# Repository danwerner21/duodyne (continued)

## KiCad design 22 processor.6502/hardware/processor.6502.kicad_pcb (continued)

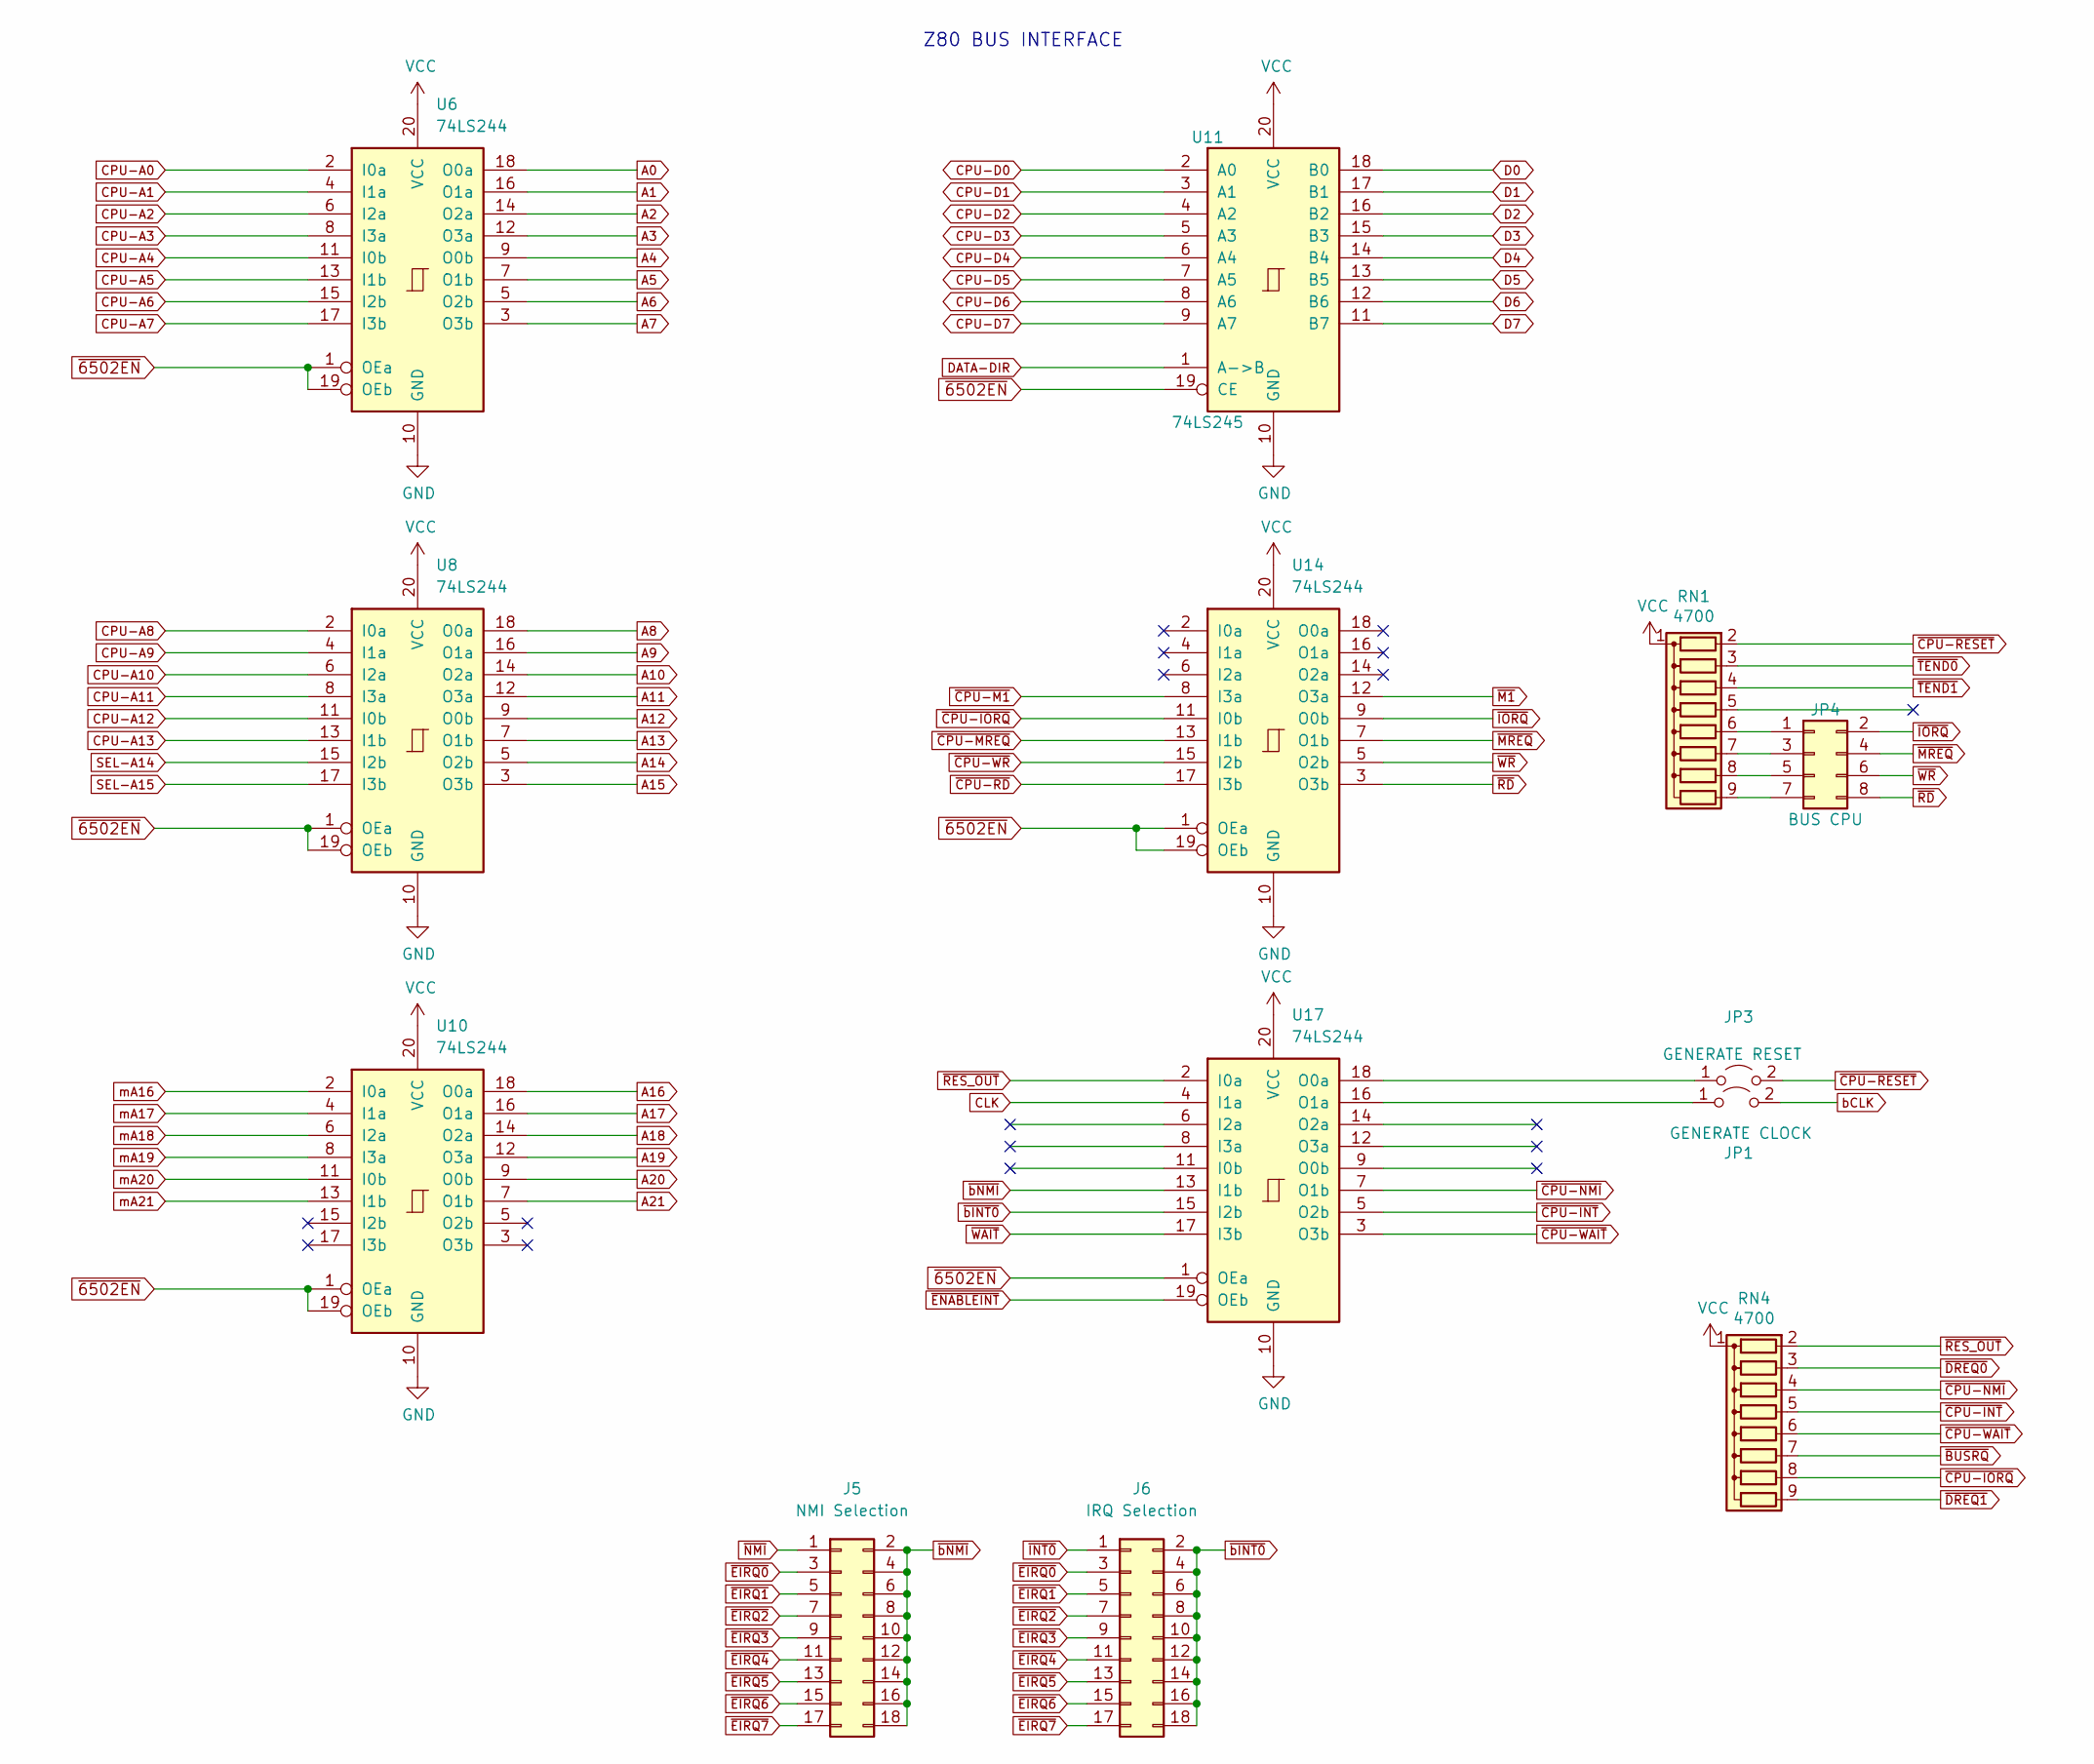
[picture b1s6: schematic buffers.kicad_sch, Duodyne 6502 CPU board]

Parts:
J5: NMI Selection; PinHeader_2x09_P2.54mm_Vertical
J6: IRQ Selection; PinHeader_2x09_P2.54mm_Vertical
JP1: GENERATE CLOCK; PinHeader_1x02_P2.54mm_Vertical
JP3: GENERATE RESET; PinHeader_1x02_P2.54mm_Horizontal
JP4: BUS CPU; PinHeader_2x04_P2.54mm_Vertical
RN1, RN4: 4700; R_Array_SIP9
U6, U8, U10, U14, U17: 74LS244; DIP-20_W7.62mm_Socket_LongPads
U11: 74LS245; DIP-20_W7.62mm_Socket_LongPads

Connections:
A0: U6.18 (O0a); also elsewhere on the board
A1: U6.16 (O1a); also elsewhere on the board
A2: U6.14 (O2a); also elsewhere on the board
A3: U6.12 (O3a); also elsewhere on the board
A4: U6.9 (O0b); also elsewhere on the board
A5: U6.7 (O1b); also elsewhere on the board
A6: U6.5 (O2b); also elsewhere on the board
A7: U6.3 (O3b); also elsewhere on the board
A8: U8.18 (O0a); also elsewhere on the board
A9: U8.16 (O1a); also elsewhere on the board
A10: U8.14 (O2a); also elsewhere on the board
A11: U8.12 (O3a); also elsewhere on the board
A12: U8.9 (O0b); also elsewhere on the board
A13: U8.7 (O1b); also elsewhere on the board
A14: U8.5 (O2b); also elsewhere on the board
A15: U8.3 (O3b); also elsewhere on the board
A16: U10.18 (O0a); also elsewhere on the board
A17: U10.16 (O1a); also elsewhere on the board
A18: U10.14 (O2a); also elsewhere on the board
A19: U10.12 (O3a); also elsewhere on the board
A20: U10.9 (O0b); also elsewhere on the board
A21: U10.7 (O1b); also elsewhere on the board
CLK: U17.4 (I1a); also elsewhere on the board
CPU-A0: U6.2 (I0a); also elsewhere on the board
CPU-A1: U6.4 (I1a); also elsewhere on the board
CPU-A2: U6.6 (I2a); also elsewhere on the board
CPU-A3: U6.8 (I3a); also elsewhere on the board
CPU-A4: U6.11 (I0b); also elsewhere on the board
CPU-A5: U6.13 (I1b); also elsewhere on the board
CPU-A6: U6.15 (I2b); also elsewhere on the board
CPU-A7: U6.17 (I3b); also elsewhere on the board
CPU-A8: U8.2 (I0a); also elsewhere on the board
CPU-A9: U8.4 (I1a); also elsewhere on the board
CPU-A10: U8.6 (I2a); also elsewhere on the board
CPU-A11: U8.8 (I3a); also elsewhere on the board
CPU-A12: U8.11 (I0b); also elsewhere on the board
CPU-A13: U8.13 (I1b); also elsewhere on the board
CPU-D0: U11.2 (A0); also elsewhere on the board
CPU-D1: U11.3 (A1); also elsewhere on the board
CPU-D2: U11.4 (A2); also elsewhere on the board
CPU-D3: U11.5 (A3); also elsewhere on the board
CPU-D4: U11.6 (A4); also elsewhere on the board
CPU-D5: U11.7 (A5); also elsewhere on the board
CPU-D6: U11.8 (A6); also elsewhere on the board
CPU-D7: U11.9 (A7); also elsewhere on the board
D0: U11.18 (B0); also elsewhere on the board
D1: U11.17 (B1); also elsewhere on the board
D2: U11.16 (B2); also elsewhere on the board
D3: U11.15 (B3); also elsewhere on the board
D4: U11.14 (B4); also elsewhere on the board
D5: U11.13 (B5); also elsewhere on the board
D6: U11.12 (B6); also elsewhere on the board
D7: U11.11 (B7); also elsewhere on the board
DATA-DIR: U11.1 (A->B); also elsewhere on the board
GND: U6.10 (GND), U8.10 (GND), U10.10 (GND), U11.10 (GND), U14.10 (GND), U17.10 (GND); also elsewhere on the board
unnamed: JP1.1 (A), U17.16 (O1a)
unnamed: JP3.1 (A), U17.18 (O0a)
unnamed: JP4.1, RN1.6 (R5)
unnamed: JP4.3, RN1.7 (R6)
unnamed: JP4.5, RN1.8 (R7)
unnamed: JP4.7, RN1.9 (R8)
SEL-A14: U8.15 (I2b); also elsewhere on the board
SEL-A15: U8.17 (I3b); also elsewhere on the board
VCC: RN1.1 (common), RN4.1 (common), U6.20 (VCC), U8.20 (VCC), U10.20 (VCC), U11.20 (VCC), U14.20 (VCC), U17.20 (VCC); also elsewhere on the board
bCLK: JP1.2 (B); also elsewhere on the board
mA16: U10.2 (I0a); also elsewhere on the board
mA17: U10.4 (I1a); also elsewhere on the board
mA18: U10.6 (I2a); also elsewhere on the board
mA19: U10.8 (I3a); also elsewhere on the board
mA20: U10.11 (I0b); also elsewhere on the board
mA21: U10.13 (I1b); also elsewhere on the board
~6502EN: U6.1 (OEa), U6.19 (OEb), U8.1 (OEa), U8.19 (OEb), U10.1 (OEa), U10.19 (OEb), U11.19 (CE), U14.1 (OEa), U14.19 (OEb), U17.1 (OEa); also elsewhere on the board
~BUSRQ: RN4.7 (R6); also elsewhere on the board
~CPU-INT: RN4.5 (R4), U17.5 (O2b); also elsewhere on the board
~CPU-IORQ: RN4.8 (R7), U14.11 (I0b); also elsewhere on the board
~CPU-M1: U14.8 (I3a); also elsewhere on the board
~CPU-MREQ: U14.13 (I1b); also elsewhere on the board
~CPU-NMI: RN4.4 (R3), U17.7 (O1b); also elsewhere on the board
~CPU-RD: U14.17 (I3b); also elsewhere on the board
~CPU-RESET: JP3.2 (B), RN1.2 (R1)
~CPU-WAIT: RN4.6 (R5), U17.3 (O3b); also elsewhere on the board
~CPU-WR: U14.15 (I2b); also elsewhere on the board
~DREQ0: RN4.3 (R2); also elsewhere on the board
~DREQ1: RN4.9 (R8); also elsewhere on the board
~EIRQ0: J5.3, J6.3; also elsewhere on the board
~EIRQ1: J5.5, J6.5; also elsewhere on the board
~EIRQ2: J5.7, J6.7; also elsewhere on the board
~EIRQ3: J5.9, J6.9; also elsewhere on the board
~EIRQ4: J5.11, J6.11; also elsewhere on the board
~EIRQ5: J5.13, J6.13; also elsewhere on the board
~EIRQ6: J5.15, J6.15; also elsewhere on the board
~EIRQ7: J5.17, J6.17; also elsewhere on the board
~ENABLEINT: U17.19 (OEb); also elsewhere on the board
~INT0: J6.1; also elsewhere on the board
~IORQ: JP4.2, U14.9 (O0b); also elsewhere on the board
~M1: U14.12 (O3a); also elsewhere on the board
~MREQ: JP4.4, U14.7 (O1b); also elsewhere on the board
~NMI: J5.1; also elsewhere on the board
~RD: JP4.8, U14.3 (O3b); also elsewhere on the board
~RES_OUT: RN4.2 (R1), U17.2 (I0a); also elsewhere on the board
~TEND0: RN1.3 (R2); also elsewhere on the board
~TEND1: RN1.4 (R3); also elsewhere on the board
~WAIT: U17.17 (I3b); also elsewhere on the board
~WR: JP4.6, U14.5 (O2b); also elsewhere on the board
~bINT0: J6.2, J6.4, J6.6, J6.8, J6.10, J6.12, J6.14, J6.16, J6.18, U17.15 (I2b)
~bNMI: J5.2, J5.4, J5.6, J5.8, J5.10, J5.12, J5.14, J5.16, J5.18, U17.13 (I1b)

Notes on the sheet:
Z80 BUS INTERFACE

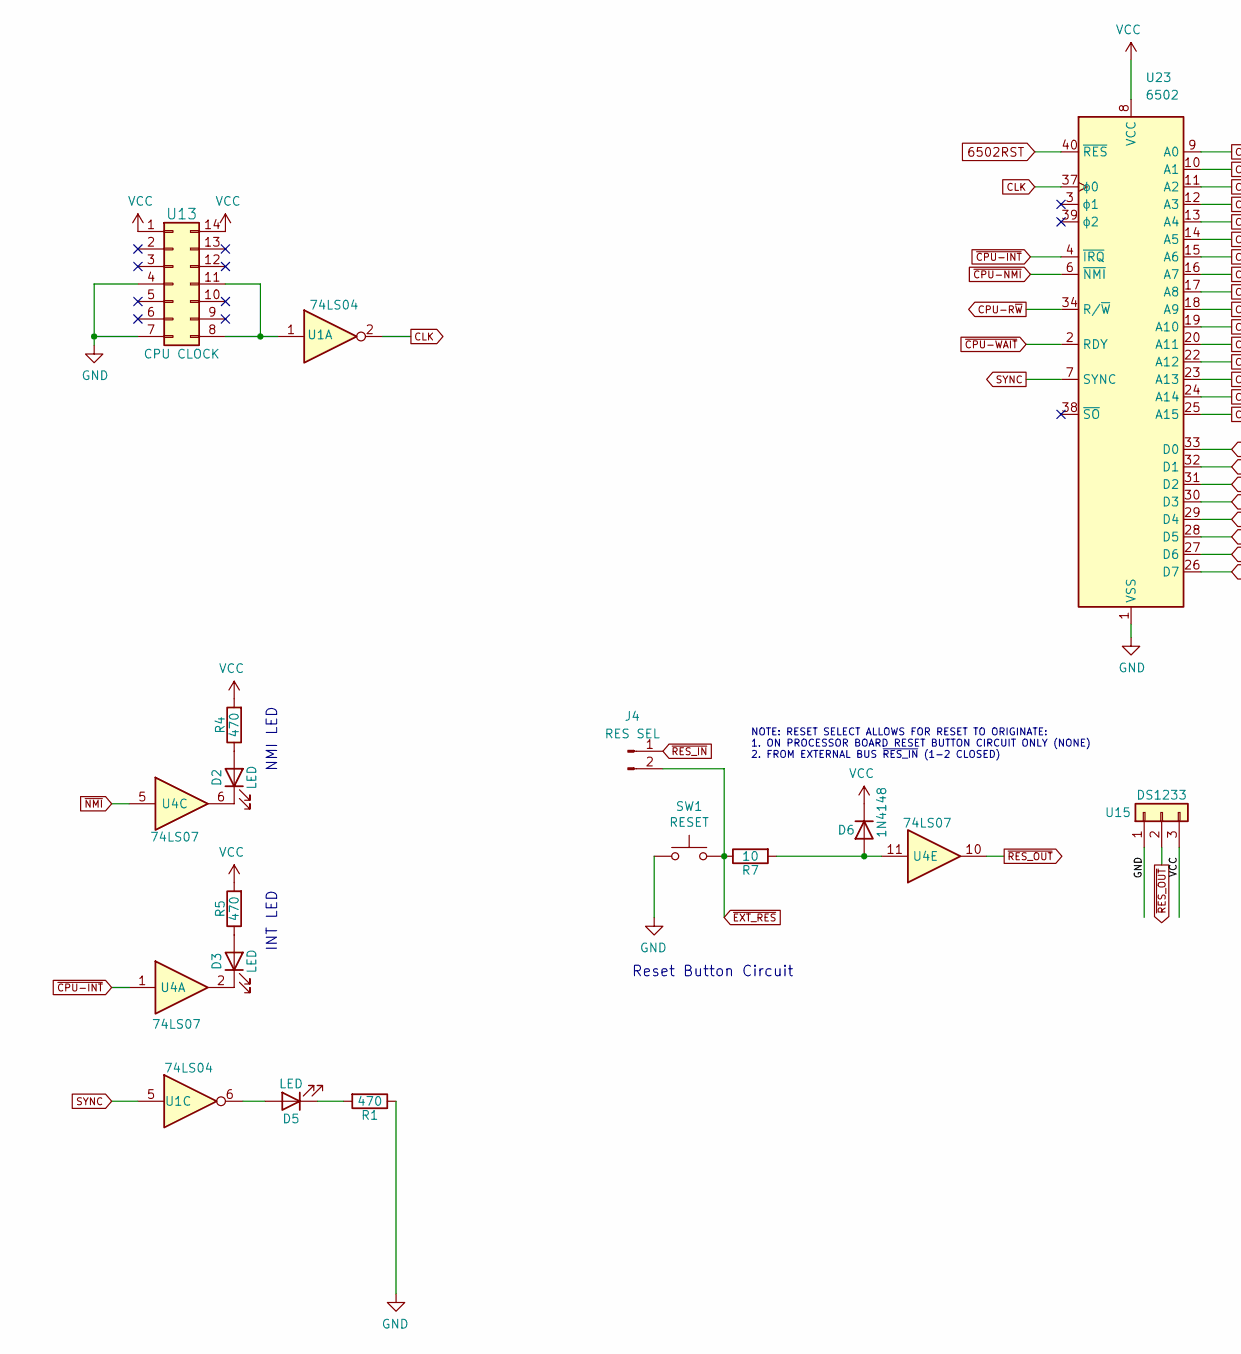
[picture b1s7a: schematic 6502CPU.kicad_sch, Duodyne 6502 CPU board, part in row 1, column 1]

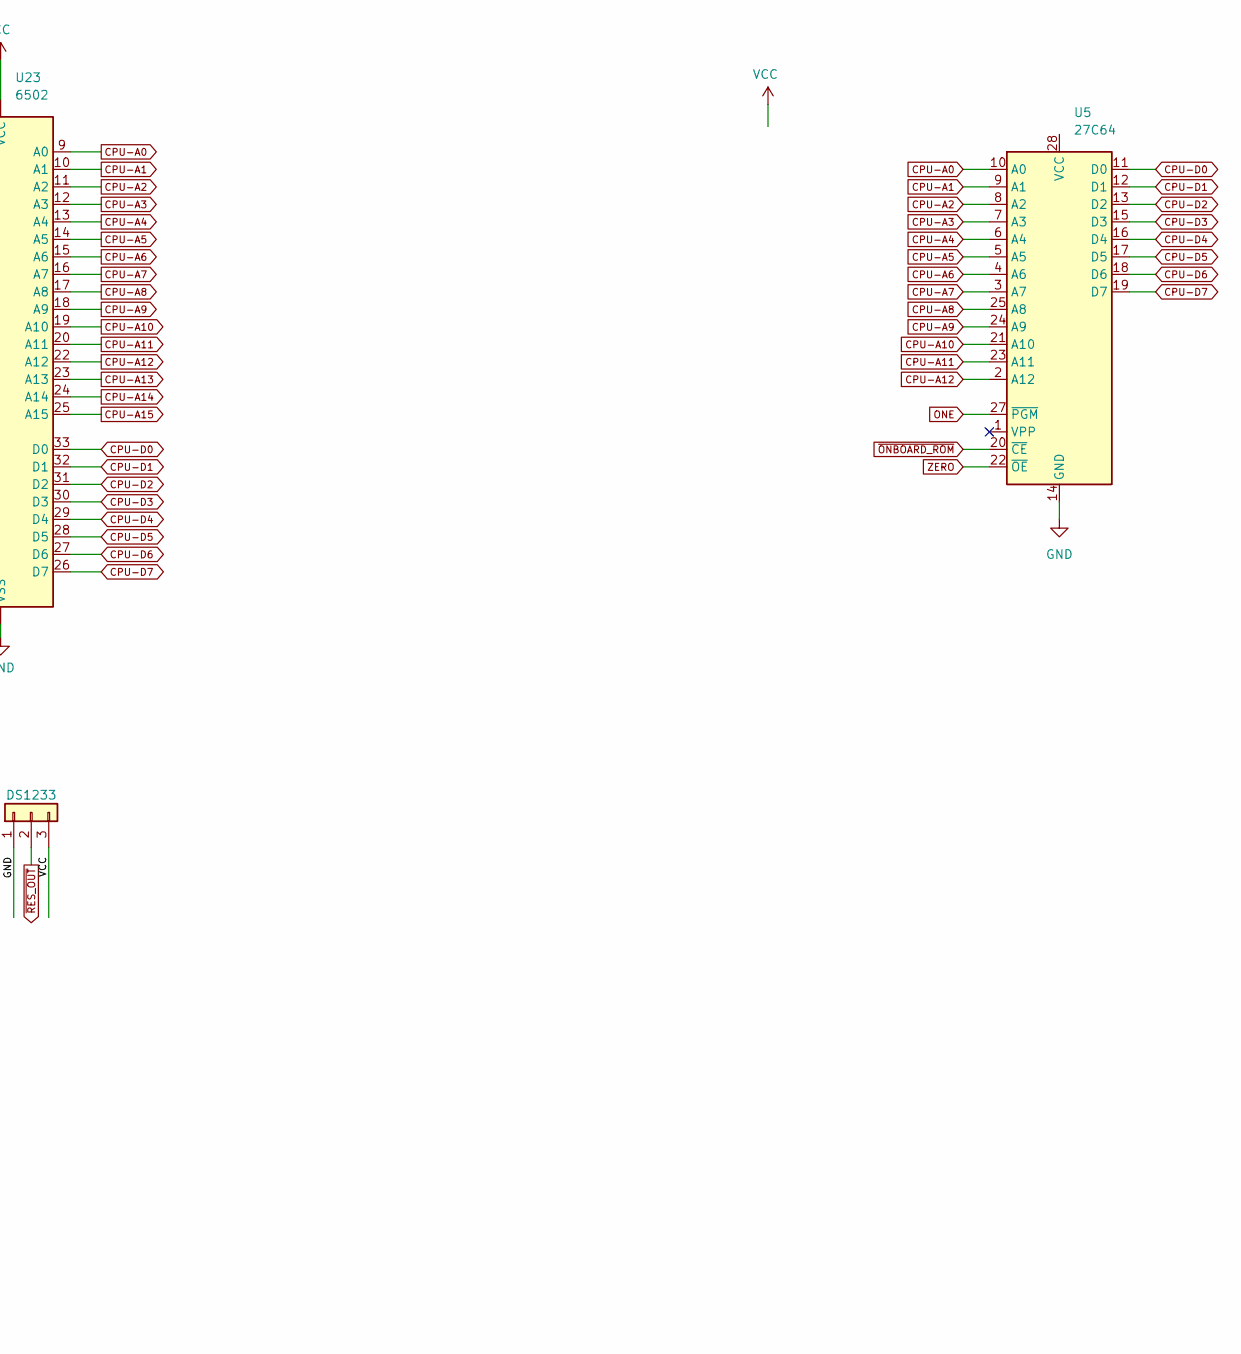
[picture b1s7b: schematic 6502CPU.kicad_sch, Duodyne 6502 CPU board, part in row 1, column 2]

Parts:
D2, D3, D5: LED; LED_D3.0mm_Horizontal_O3.81mm_Z2.0mm
D6: 1N4148; D_DO-35_SOD27_P7.62mm_Horizontal
J4: RES SEL; PinHeader_1x02_P2.54mm_Vertical
R1, R4, R5: 470; R_Axial_DIN0207_L6.3mm_D2.5mm_P7.62mm_Horizontal
R7: 10; R_Axial_DIN0207_L6.3mm_D2.5mm_P7.62mm_Horizontal
SW1: RESET; SW_Tactile_SPST_Angled_PTS645Vx58-2LFS
U1: 74LS04; DIP-14_W7.62mm_Socket_LongPads
U4: 74LS07; DIP-14_W7.62mm_Socket_LongPads
U5: 27C64; DIP-28_W15.24mm
U13: CPU CLOCK; DIP-14_W7.62mm_Socket_LongPads
U15: DS1233; TO-92L_HandSolder
U23: 6502; DIP-40_W15.24mm_Socket_LongPads

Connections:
6502RST: U23.40 (~RES); also elsewhere on the board
CLK: U1.2, U23.37 (ϕ0); also elsewhere on the board
CPU-A0: U5.10 (A0), U23.9 (A0); also elsewhere on the board
CPU-A1: U5.9 (A1), U23.10 (A1); also elsewhere on the board
CPU-A2: U5.8 (A2), U23.11 (A2); also elsewhere on the board
CPU-A3: U5.7 (A3), U23.12 (A3); also elsewhere on the board
CPU-A4: U5.6 (A4), U23.13 (A4); also elsewhere on the board
CPU-A5: U5.5 (A5), U23.14 (A5); also elsewhere on the board
CPU-A6: U5.4 (A6), U23.15 (A6); also elsewhere on the board
CPU-A7: U5.3 (A7), U23.16 (A7); also elsewhere on the board
CPU-A8: U5.25 (A8), U23.17 (A8); also elsewhere on the board
CPU-A9: U5.24 (A9), U23.18 (A9); also elsewhere on the board
CPU-A10: U5.21 (A10), U23.19 (A10); also elsewhere on the board
CPU-A11: U5.23 (A11), U23.20 (A11); also elsewhere on the board
CPU-A12: U5.2 (A12), U23.22 (A12); also elsewhere on the board
CPU-A13: U23.23 (A13); also elsewhere on the board
CPU-A14: U23.24 (A14); also elsewhere on the board
CPU-A15: U23.25 (A15); also elsewhere on the board
CPU-D0: U5.11 (D0), U23.33 (D0); also elsewhere on the board
CPU-D1: U5.12 (D1), U23.32 (D1); also elsewhere on the board
CPU-D2: U5.13 (D2), U23.31 (D2); also elsewhere on the board
CPU-D3: U5.15 (D3), U23.30 (D3); also elsewhere on the board
CPU-D4: U5.16 (D4), U23.29 (D4); also elsewhere on the board
CPU-D5: U5.17 (D5), U23.28 (D5); also elsewhere on the board
CPU-D6: U5.18 (D6), U23.27 (D6); also elsewhere on the board
CPU-D7: U5.19 (D7), U23.26 (D7); also elsewhere on the board
CPU-R~W: U23.34 (R/~W); also elsewhere on the board
GND: R1.1, SW1.2, U5.14 (GND), U13.4, U13.7, U15.1, U23.1 (VSS), U23.21 (VSS); also elsewhere on the board
unnamed: D2.1 (K), U4.6
unnamed: D2.2 (A), R4.1
unnamed: D3.1 (K), U4.2
unnamed: D3.2 (A), R5.1
unnamed: D5.1 (K), R1.2
unnamed: D5.2 (A), U1.6
unnamed: D6.2 (A), R7.2, U4.11
unnamed: U1.1, U13.8, U13.11
ONE: U5.27 (~PGM); also elsewhere on the board
SYNC: U1.5, U23.7 (SYNC)
VCC: D6.1 (K), R4.2, R5.2, U13.1, U13.14, U15.3, U23.8 (VCC); also elsewhere on the board
ZERO: U5.22 (~OE); also elsewhere on the board
~CPU-INT: U4.1, U23.4 (~IRQ); also elsewhere on the board
~CPU-NMI: U23.6 (~NMI); also elsewhere on the board
~CPU-WAIT: U23.2 (RDY); also elsewhere on the board
~EXT_RES: J4.2, R7.1, SW1.1; also elsewhere on the board
~NMI: U4.5; also elsewhere on the board
~ONBOARD_ROM: U5.20 (~CE); also elsewhere on the board
~RES_IN: J4.1; also elsewhere on the board
~RES_OUT: U4.10, U15.2; also elsewhere on the board

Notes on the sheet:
Reset Button Circuit
NMI LED
INT LED
NOTE: RESET SELECT ALLOWS FOR RESET TO ORIGINATE: 1. ON PROCESSOR BOARD RESET BUTTON CIRCUIT ONLY (NONE) 2. FROM EXTERNAL BUS ~{RES_IN} (1-2 CLOSED)

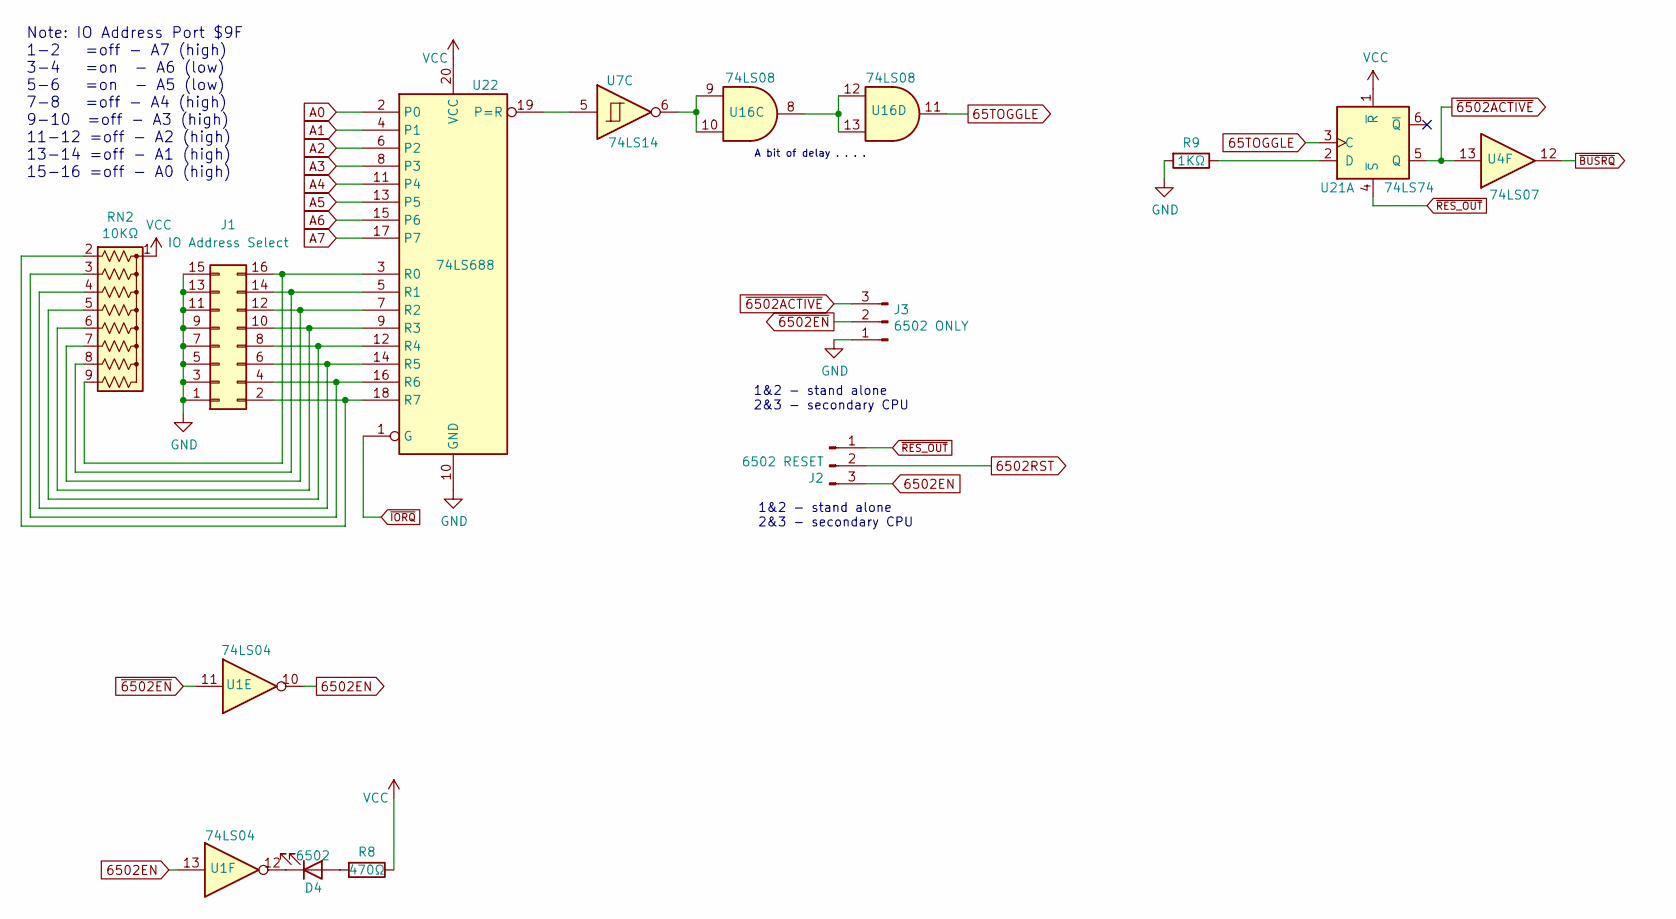
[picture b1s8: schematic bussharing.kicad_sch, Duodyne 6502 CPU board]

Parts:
D4: 6502; LED_D3.0mm_Horizontal_O3.81mm_Z2.0mm
J1: IO Address Select; PinHeader_2x08_P2.54mm_Vertical
J2: 6502 RESET; PinHeader_1x03_P2.54mm_Horizontal
J3: 6502 ONLY; PinHeader_1x03_P2.54mm_Horizontal
R8: 470Ω; R_Axial_DIN0207_L6.3mm_D2.5mm_P7.62mm_Horizontal
R9: 1KΩ; R_Axial_DIN0207_L6.3mm_D2.5mm_P7.62mm_Horizontal
RN2: 10KΩ; R_Array_SIP9
U1: 74LS04; DIP-14_W7.62mm_Socket_LongPads
U4: 74LS07; DIP-14_W7.62mm_Socket_LongPads
U7: 74LS14; DIP-14_W7.62mm_Socket_LongPads
U16: 74LS08; DIP-14_W7.62mm_Socket_LongPads
U21: 74LS74; DIP-14_W7.62mm_Socket_LongPads
U22: 74LS688; DIP-20_W7.62mm_Socket_LongPads

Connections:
65TOGGLE: U16.11, U21.3 (C)
6502EN: J2.3, U1.10, U1.13
6502RST: J2.2; also elsewhere on the board
A0: U22.2 (P0); also elsewhere on the board
A1: U22.4 (P1); also elsewhere on the board
A2: U22.6 (P2); also elsewhere on the board
A3: U22.8 (P3); also elsewhere on the board
A4: U22.11 (P4); also elsewhere on the board
A5: U22.13 (P5); also elsewhere on the board
A6: U22.15 (P6); also elsewhere on the board
A7: U22.17 (P7); also elsewhere on the board
GND: J1.1, J1.3, J1.5, J1.7, J1.9, J1.11, J1.13, J1.15, J3.1, R9.2, U22.10 (GND); also elsewhere on the board
unnamed: D4.1 (K), U1.12
unnamed: D4.2 (A), R8.2
unnamed: J1.2, RN2.2 (R1), U22.18 (R7)
unnamed: J1.4, RN2.3 (R2), U22.16 (R6)
unnamed: J1.6, RN2.4 (R3), U22.14 (R5)
unnamed: J1.8, RN2.5 (R4), U22.12 (R4)
unnamed: J1.10, RN2.6 (R5), U22.9 (R3)
unnamed: J1.12, RN2.7 (R6), U22.7 (R2)
unnamed: J1.14, RN2.8 (R7), U22.5 (R1)
unnamed: J1.16, RN2.9 (R8), U22.3 (R0)
unnamed: R9.1, U21.2 (D)
unnamed: U7.6, U16.9, U16.10
unnamed: U16.8, U16.12, U16.13
unnamed: U7.5, U22.19 (P=R)
VCC: R8.1, RN2.1 (common), U21.1 (~R), U22.20 (VCC); also elsewhere on the board
~6502ACTIVE: J3.3, U4.13, U21.5 (Q)
~6502EN: J3.2, U1.11; also elsewhere on the board
~BUSRQ: U4.12; also elsewhere on the board
~IORQ: U22.1 (G); also elsewhere on the board
~RES_OUT: J2.1, U21.4 (~S); also elsewhere on the board

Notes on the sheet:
1&2 - stand alone 2&3 - secondary CPU
A bit of delay . . . .
Note: IO Address Port $9F 1-2 =off - A7 (high) 3-4 =on - A6 (low) 5-6 =on - A5 (low) 7-8 =off - A4 (high) 9-10 =off - A3 (high) 11-12 =off - A2 (high) 13-14 =off - A1 (high) 15-16 =off - A0 (high)

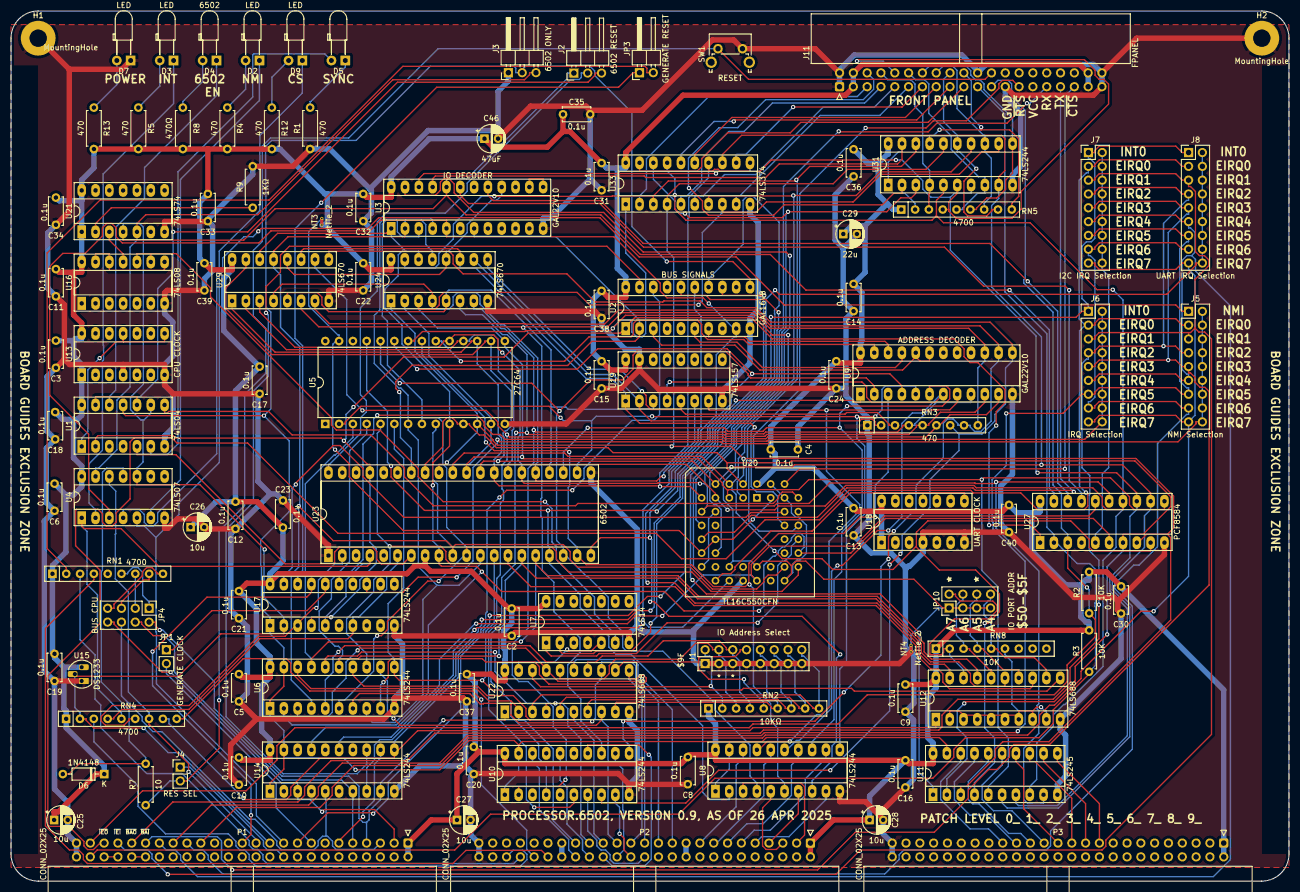
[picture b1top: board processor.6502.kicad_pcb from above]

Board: 2 copper layers, 235.0 x 160.0 mm, 111 parts (0 on the bottom side), 195 nets.

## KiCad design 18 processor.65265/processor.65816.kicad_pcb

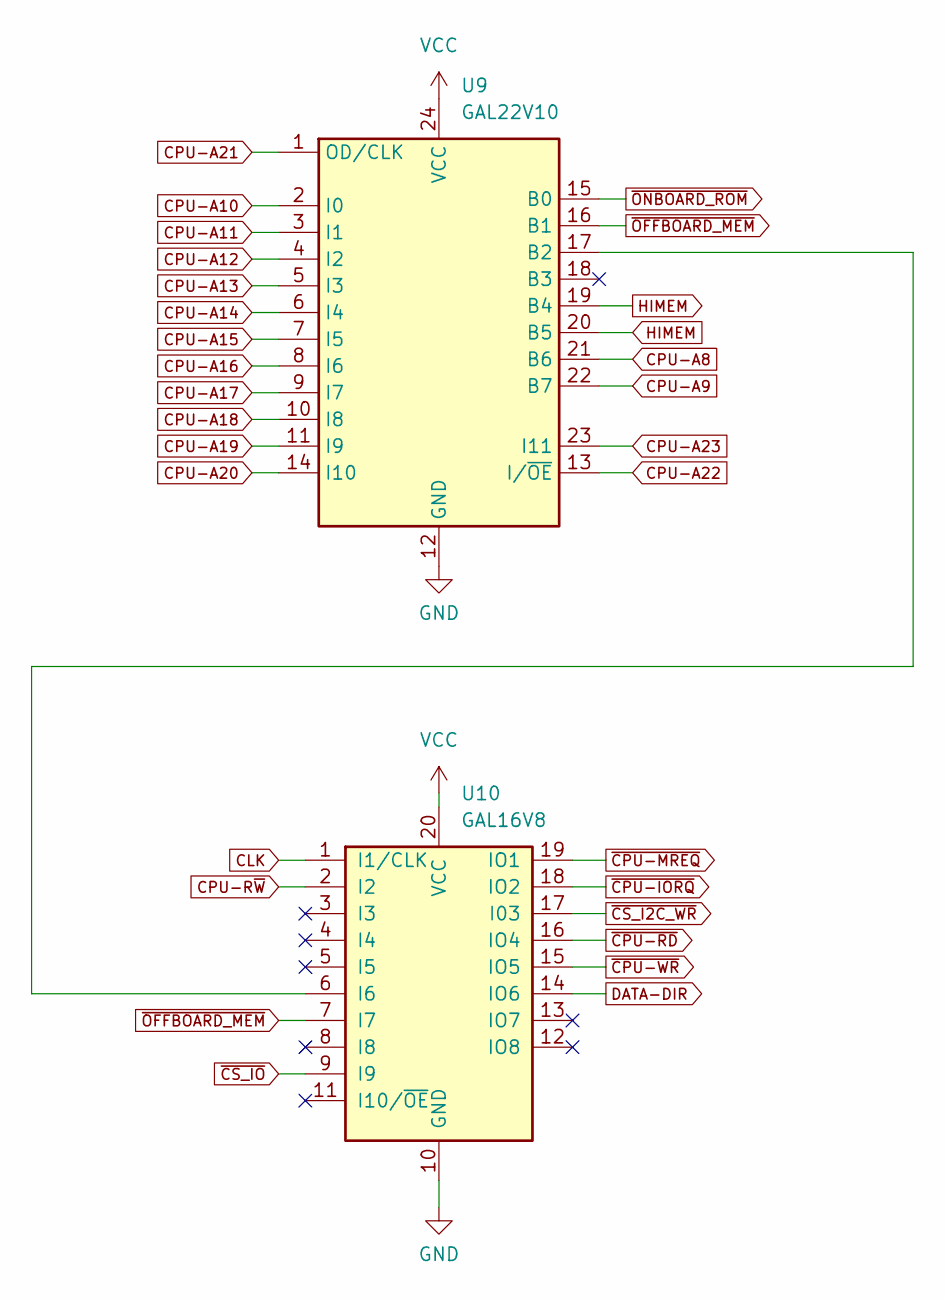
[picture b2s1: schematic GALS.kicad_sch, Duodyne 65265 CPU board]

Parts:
U9: GAL22V10; DIP-24_W7.62mm_Socket_LongPads
U10: GAL16V8; DIP-20_W7.62mm_Socket_LongPads

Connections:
CLK: U10.1 (I1/CLK); also elsewhere on the board
CPU-A8: U9.21 (B6); also elsewhere on the board
CPU-A9: U9.22 (B7); also elsewhere on the board
CPU-A10: U9.2 (I0); also elsewhere on the board
CPU-A11: U9.3 (I1); also elsewhere on the board
CPU-A12: U9.4 (I2); also elsewhere on the board
CPU-A13: U9.5 (I3); also elsewhere on the board
CPU-A14: U9.6 (I4); also elsewhere on the board
CPU-A15: U9.7 (I5); also elsewhere on the board
CPU-A16: U9.8 (I6); also elsewhere on the board
CPU-A17: U9.9 (I7); also elsewhere on the board
CPU-A18: U9.10 (I8); also elsewhere on the board
CPU-A19: U9.11 (I9); also elsewhere on the board
CPU-A20: U9.14 (I10); also elsewhere on the board
CPU-A21: U9.1 (OD/CLK); also elsewhere on the board
CPU-A22: U9.13 (I/~OE); also elsewhere on the board
CPU-A23: U9.23 (I11); also elsewhere on the board
CPU-R~W: U10.2 (I2); also elsewhere on the board
DATA-DIR: U10.14 (IO6); also elsewhere on the board
GND: U9.12 (GND), U10.10 (GND); also elsewhere on the board
HIMEM: U9.19 (B4), U9.20 (B5)
unnamed: U9.17 (B2), U10.6 (I6)
VCC: U9.24 (VCC), U10.20 (VCC); also elsewhere on the board
~CPU-IORQ: U10.18 (IO2); also elsewhere on the board
~CPU-MREQ: U10.19 (IO1); also elsewhere on the board
~CPU-RD: U10.16 (IO4); also elsewhere on the board
~CPU-WR: U10.15 (IO5); also elsewhere on the board
~CS_I2C_WR: U10.17 (I03); also elsewhere on the board
~CS_IO: U10.9 (I9); also elsewhere on the board
~OFFBOARD_MEM: U9.16 (B1), U10.7 (I7)
~ONBOARD_ROM: U9.15 (B0); also elsewhere on the board
